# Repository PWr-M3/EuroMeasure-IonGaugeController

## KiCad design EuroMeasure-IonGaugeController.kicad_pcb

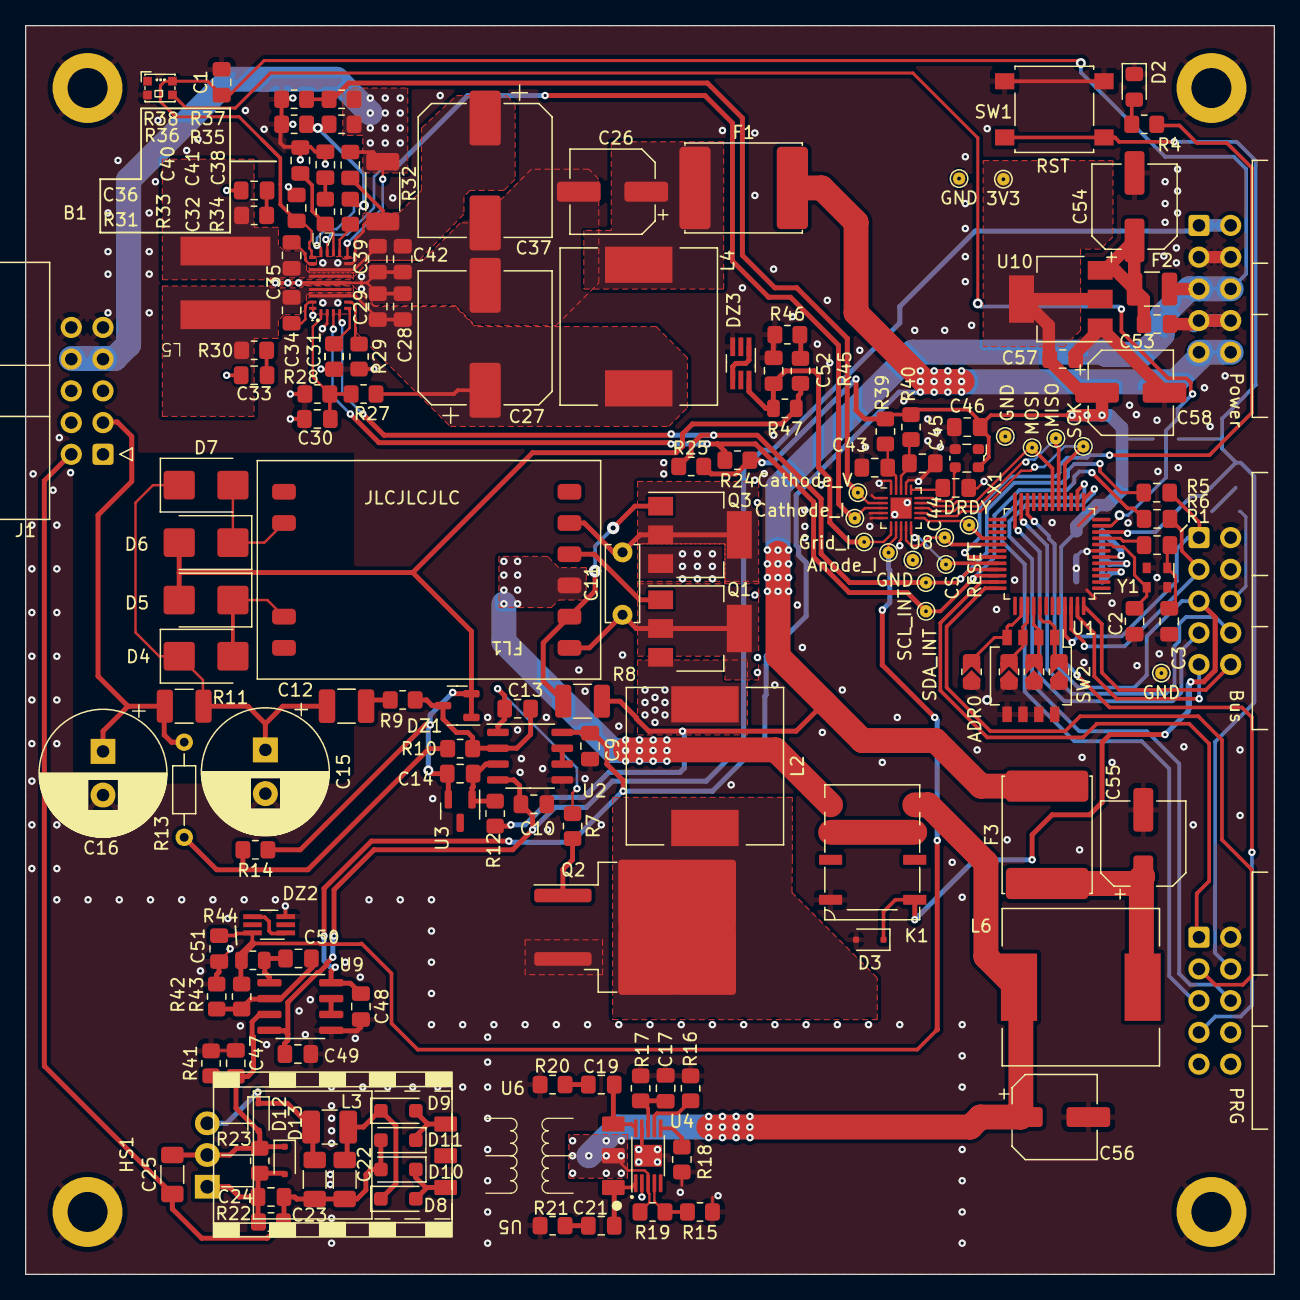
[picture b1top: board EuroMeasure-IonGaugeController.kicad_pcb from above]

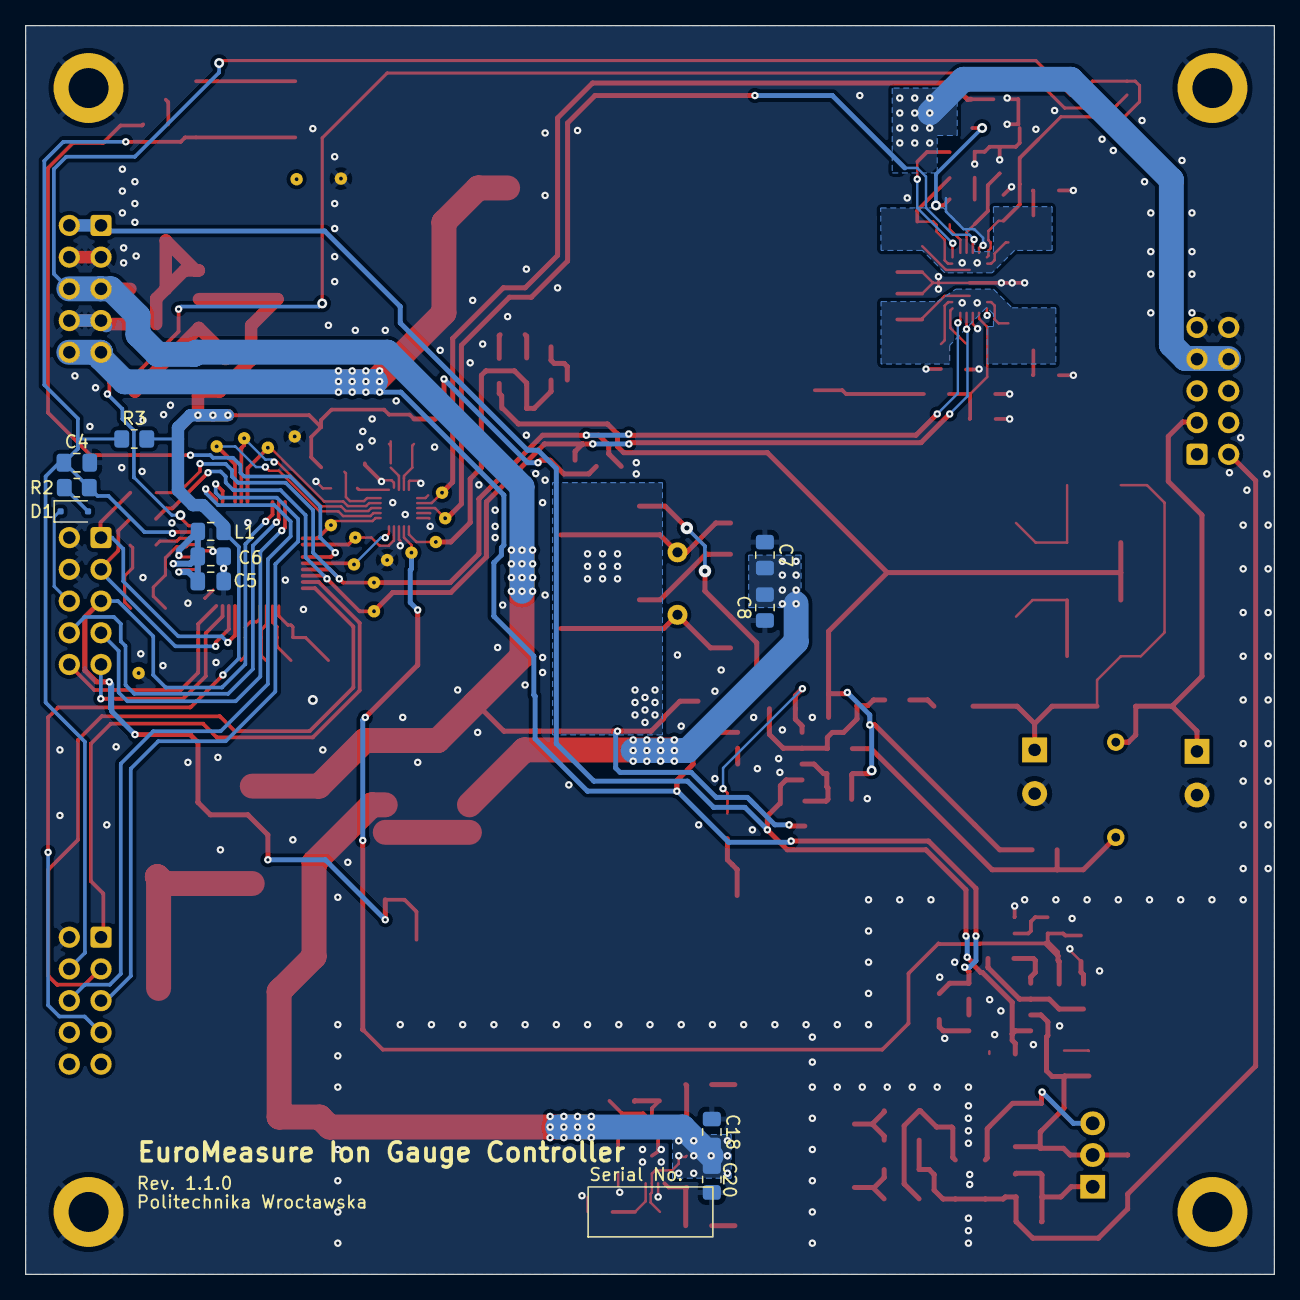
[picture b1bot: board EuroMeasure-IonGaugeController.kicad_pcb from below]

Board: 2 copper layers, 100.0 x 100.0 mm, 173 parts (11 on the bottom side), 107 nets.

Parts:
B1: EuroBoard; EuroMeasureLED
C1, C6, C7, C8, C18, C20, C24, C28, C29, C32, C39, C42, C43, C44, C45, C53, C57: 10u; C_0805_2012Metric_Pad1.18x1.45mm_HandSolder
C2, C3: 8p; C_0805_2012Metric_Pad1.18x1.45mm_HandSolder
C4, C5, C9, C10, C13, C14, C30, C34, C35, C38, C41, C46, C47, C48, C49: 100n; C_0805_2012Metric_Pad1.18x1.45mm_HandSolder
C11: 220n; C_Disc_D6.0mm_W2.5mm_P5.00mm
C12: 1n X7R; C_1210_3225Metric_Pad1.33x2.70mm_HandSolder
C15, C16: 3.3u 400V; CP_Radial_D10.0mm_P3.50mm
C17: 1uF; C_0805_2012Metric_Pad1.18x1.45mm_HandSolder
C19, C21, C33, C36: C_0805_2012Metric_Pad1.18x1.45mm_HandSolder
C22, C23, C25: 10u; C_1206_3216Metric_Pad1.33x1.80mm_HandSolder
C26, C55, C56: 220uF 50V; CP_Elec_6.3x7.7
C27, C37: 330uF 25V; CP_Elec_10x12.5
C31, C51, C52: 10n; C_0805_2012Metric_Pad1.18x1.45mm_HandSolder
C40: 100p; C_0805_2012Metric_Pad1.18x1.45mm_HandSolder
C50: 200p C0G; C_0805_2012Metric_Pad1.18x1.45mm_HandSolder
C54, C58: 220u; CP_Elec_6.3x7.7
D1, D3, D12, D13: 1N4148; D_SOD-323F
D2: RED; LED_0805_2012Metric_Pad1.15x1.40mm_HandSolder
D4, D5, D6, D7: MURS160BJ; D_SMB
D8: D_PMEG200G20ELRX; D_SOD-123F
D9, D10, D11: MURS160BJ; D_SOD-123F
DZ1: 14V; SOT-23-3
DZ2, DZ3: 2V4; SOT-363_SC-70-6_Handsoldering
F1, F3: Polyfuse 2A; Fuse_Littlefuse_3425L
F2: Polyfuse 0.5A; Fuse_1210_3225Metric
FL1: FL2015-4L; T_FL2015
HS1: Heatsink 274-3AB; 274-3AB
J1: Gauge Connector; IDC-Header_2x05_P2.54mm_Horizontal
JP1: ADR0; R_0805_2012Metric_Jumper
JP2: ADR1; R_0805_2012Metric_Jumper
JP3: ADR2; R_0805_2012Metric_Jumper
JP4: ADR3; R_0805_2012Metric_Jumper
K1: UD2-5NU; Relay_DPDT_Kemet_UC2_NU
L1: Ferrite; L_0805_2012Metric_Pad1.15x1.40mm_HandSolder
L2, L4, L6: 220u; L_12x12mm_H8mm
L3: 220u; L_1210_3225Metric_Pad1.42x2.65mm_HandSolder
L5: 8.2u; L_Bourns_SRP7030
Q1, Q3: FZT1053A; SOT-223-3_TabPin2
Q2: IRF540SPBF; TO-263-2
R1, R5, R6: 0R; C_0805_2012Metric_Pad1.18x1.45mm_HandSolder
R2, R3, R4, R9, R24, R25, R28, R38: 1k; R_0805_2012Metric_Pad1.20x1.40mm_HandSolder
R7, R12, R27, R37: 10k; R_0805_2012Metric_Pad1.20x1.40mm_HandSolder
R8: R_1210_820Ohm; R_1210_3225Metric_Pad1.30x2.65mm_HandSolder
R10: 470k; R_0805_2012Metric_Pad1.20x1.40mm_HandSolder
R11: 1k 0.5W; R_1210_3225Metric_Pad1.30x2.65mm_HandSolder
R13: 2M; R_Axial_DIN0204_L3.6mm_D1.6mm_P7.62mm_Horizontal
R14: 30k; R_0805_2012Metric_Pad1.20x1.40mm_HandSolder
R15: 1.5k; R_0805_2012Metric_Pad1.20x1.40mm_HandSolder
R16: 22k; R_0805_2012Metric_Pad1.20x1.40mm_HandSolder
R17: 50k; R_0805_2012Metric_Pad1.20x1.40mm_HandSolder
R18: 21k; R_0805_2012Metric_Pad1.20x1.40mm_HandSolder
R19: 2.2k; R_0805_2012Metric_Pad1.20x1.40mm_HandSolder
R20, R21, R30, R31: R_0805_2012Metric_Pad1.20x1.40mm_HandSolder
R22: 4.7k; R_0805_2012Metric_Pad1.20x1.40mm_HandSolder
R23: 240R; R_0805_2012Metric_Pad1.20x1.40mm_HandSolder
R26, R34: 0R; R_0805_2012Metric_Pad1.20x1.40mm_HandSolder
R29: 47k; R_0805_2012Metric_Pad1.20x1.40mm_HandSolder
R32: 20m 1%; R_2010_5025Metric_Pad1.40x2.65mm_HandSolder
R33, R36: 8.2k; R_0805_2012Metric_Pad1.20x1.40mm_HandSolder
R35: 100k; R_0805_2012Metric_Pad1.20x1.40mm_HandSolder
R39: 1; R_0805_2012Metric_Pad1.20x1.40mm_HandSolder
R40: 10; R_0805_2012Metric_Pad1.20x1.40mm_HandSolder
R41, R42: 1k 0.1% 5PPM; R_0805_2012Metric_Pad1.20x1.40mm_HandSolder
R43: 10k 0.1% 5PPM; R_0805_2012Metric_Pad1.20x1.40mm_HandSolder
R44, R47: 1k; R_0805_2012Metric
R45, R46: 100R 0.1% 5PPM; R_0805_2012Metric_Pad1.20x1.40mm_HandSolder
SW1: RST; SW_SPST_B3S-1000
SW2: SW_DIP_x04; SW_DIP_SPSTx04_Slide_Omron_A6H-4101_W6.15mm_P1.27mm
TP1: Cathode_V; TestPoint_Pad_D1.0mm
TP2: Cathode_I; TestPoint_Pad_D1.0mm
TP3: Anode_I; TestPoint_Pad_D1.0mm
TP4: Grid_I; TestPoint_Pad_D1.0mm
TP5, TP6, TP7, TP8: GND; TestPoint_Pad_D1.0mm
TP9: SCK; TestPoint_Pad_D1.0mm
TP10: MISO; TestPoint_Pad_D1.0mm
TP11: MOSI; TestPoint_Pad_D1.0mm
TP12: DRDY; TestPoint_Pad_D1.0mm
TP13: RESET; TestPoint_Pad_D1.0mm
TP14: CS; TestPoint_Pad_D1.0mm
TP15: SCL_INT; TestPoint_Pad_D1.0mm
TP16: SDA_INT; TestPoint_Pad_D1.0mm
TP17: 3V3; TestPoint_Pad_D1.0mm
U1: STM32G030CxT; LQFP-48_7x7mm_P0.5mm
U2: TL072; SO-8_3.9x4.9mm_P1.27mm
U3: 3.0V; SOT-23
U4: SN6507
U5: T_750316856; 750316856
U6: LM317HVT_TO-220-3; TO-220-3_Horizontal_TabUp
U7: TPS55289
U8: ADS131M04-WQFN; WQFN-20-1EP_3x3mm_P0.4mm_EP1.7x1.7mm
U9: OPA2187; SOIC-8_3.9x4.9mm_P1.27mm
U10: AZ1117-3V3; SOT-223-3_TabPin2
X1: 8.192MHz; Oscillator_SMD_ECS_2520MV-xxx-xx-4Pin_2.5x2.0mm
Y1: 16MHz; Oscillator_SMD_Abracon_ASDMB-4Pin_2.5x2.0mm

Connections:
+3.3V: B1.27 (3.3V), C46.2, C57.1, C58.1, L1.1, R3.2, R24.1, R25.1, R39.2, R40.2, TP17.1, U10.2 (VO), X1.4 (VDD)
+5V: B1.5 (5V), B1.6 (5V), B1.D4 (VCC), C1.1, C32.2, F2.1, F3.2, R8.2, R12.1, U7.18 (VCC)
+15V: B1.9 (15V), B1.10 (15V), C9.2, C48.1, F1.2, U2.8 (V+), U9.8 (V+)
-15V: B1.1 (-15V), B1.2 (-15V), C10.1, C49.2, U2.4 (V-), U9.4 (V-)
/ADC/1: R37.2, R38.1, TP1.1, U8.2 (AIN0N)
/ADC/2: TP2.1, U7.16 (CDC), U8.3 (AIN1N)
/ADC/3: C52.1, DZ3.6 (K), R47.2, TP4.1, U8.6 (AIN2N)
/ADC/4: C51.1, DZ2.6 (K), R43.2, R44.2, TP3.1, U8.7 (AIN3N)
/ADC/CLK: U8.15 (CLKIN), X1.3 (OUT)
/ADC/CS: TP14.1, U1.32 (PA10), U8.10 (~CS)
/ADC/DIN: TP11.1, U1.18 (PA7), U8.14 (DIN)
/ADC/DOUT: TP10.1, U1.17 (PA6), U8.13 (DOUT)
/ADC/DRDY: TP12.1, U1.28 (PA8), U8.11 (~DRDY)
/ADC/RESET: TP13.1, U1.29 (PA9), U8.9 (~SYNC/~RESET)
/ADC/SCLK: TP9.1, U1.16 (PA5), U8.12 (SCLK)
/ANODE: C22.1, C23.1, C24.1, C25.1, D10.2 (A), D11.2 (A), J1.2, R22.2
/Anode Current Measurement/IN: C25.2, C47.1, D12.2 (A), D13.1 (K), R23.1, R41.1, U6.2 (VO), U9.3 (+)
/Anode Supply/5V_IN: C18.2, C20.2, C56.1, K1.4, L6.2, R19.2, U4.3 (VCC), U5.2
/Anode Supply/SW1: C21.1, U4.1 (SW1), U5.1
/Anode Supply/SW2: C19.1, U4.10 (SW2), U5.3
/Backplane connector/GP0: B1.17 (GP0), U1.24 (PB12)
/Backplane connector/GP1: B1.18 (GP1), U1.23 (PB11)
/Backplane connector/RDY: B1.20 (RDY), U1.48 (PB9)
/Backplane connector/RST: B1.16 (RST), D1.1 (K)
/Backplane connector/RST_LOCAL: B1.24 (RST), C4.1, R2.1, R3.1, SW1.2, U1.10 (NRST)
/Backplane connector/RX: B1.25 (RX), U1.14 (PA3)
/Backplane connector/SCL: B1.11 (SCL), R5.1, U1.45 (PB6)
/Backplane connector/SDA: B1.13 (SDA), R6.2, U1.46 (PB7)
/Backplane connector/SWCLK: B1.23 (SWCLK), U1.36 (PA14)
/Backplane connector/SWDIO: B1.21 (SWDIO), U1.35 (PA13)
/Backplane connector/TRG: B1.19 (TRG), U1.47 (PB8)
/Backplane connector/TX: B1.26 (TX), U1.13 (PA2)
/Backplane connector/~LOCKOUT: B1.15 (~LOCKOUT), D3.1 (K), K1.1, U1.22 (PB10)
/CATHODE: C38.2, J1.7, J1.8, R32.2, R35.1, R37.1, U7.13 (ISN)
/Cathode Supply/15V_FILTERED: C27.1, C28.2, C29.2, L4.2, R27.1, U7.7 (VIN)
/Cathode Supply/SCL: R5.2, R25.2, TP15.1, U1.33 (PA11), U7.4 (SDA)
/Cathode Supply/SDA: R6.1, R24.2, TP16.1, U1.34 (PA12), U7.3 (SCL)
/Cathode Supply/SW1: C34.1, L5.1, R30.2, U7.8 (SW1)
/GRID: C16.1, J1.3, R11.2, R13.2
/Grid Supply/5V_Lockouted: C7.2, C8.2, FL1.3, K1.5
/Grid Supply/GRID_AC0: D4.2 (A), D5.1 (K), FL1.9
/Grid Supply/GRID_AC1: D6.1 (K), D7.2 (A), FL1.8
/Grid Supply/GRID_Unfiltered: C12.1, C15.1, D4.1 (K), D7.1 (K), R11.1
/Grid Supply/heatsink_1: C11.1, FL1.1, Q1.2 (C)
/Grid Supply/heatsink_2: C11.2, FL1.5, Q3.2 (C)
/Grid Supply/heatsink_3: L2.1, Q1.3 (E), Q3.3 (E)
/Grid Supply/heatsink_4: L2.2, Q2.2 (D)
/MCU/3V3_MCU: C5.1, C6.1, L1.2, U1.4 (VBAT), U1.5 (VREF+), U1.6 (VDD/VDDA)
/MCU/ADR0: JP1.1, SW2.4, U1.38 (PD0)
/MCU/ADR1: JP2.1, SW2.3, U1.39 (PD1)
/MCU/ADR2: JP3.1, SW2.2, U1.40 (PD2)
/MCU/ADR3: JP4.1, SW2.1, U1.41 (PD3)
/MCU/LED: R4.2, U1.31 (PC7)
/MCU/OSC_IN: R1.2, U1.9 (PF1-OSC_OUT)
/MCU/OSC_OUT: C2.1, U1.8 (PF0-OSC_IN), Y1.3
/MCU/RGB_LED: B1.D3 (DI), U1.11 (PA0)
/PSU/5V_FUSED: C53.1, C54.1, F2.2, U10.3 (VI)
GND: B1.3 (GND), B1.4 (GND), B1.7 (GND), B1.8 (GND), B1.12 (GND), B1.14 (GND), B1.22 (GND), B1.D2 (GND), C1.2, C2.2, C3.2, C4.2, C5.2, C6.2, C7.1, C8.1, C9.1, C10.2, C15.2, C16.2, C17.1, C18.1, C20.1, C26.2, C27.2, C28.1, C29.1, C30.1, C31.2, C32.1, C33.2, C36.2, C37.2, C39.1, C40.1, C41.1, C42.1, C43.1, C44.2, C45.2, C46.1, C47.2, C48.2, C49.1, C51.2, C52.2, C53.2, C54.2, C55.2, C56.2, C57.2, C58.2, D2.1 (K), D3.2 (A), DZ2.3 (K), DZ3.3 (K), J1.9, J1.10, JP1.2, JP2.2, JP3.2, JP4.2, K1.8, Q2.3 (S), R15.1, R16.1, R17.1, R18.1, R20.2, R21.2, R26.2, R28.2, R29.2, R36.2, R38.2, R41.2, R42.2, R46.2, SW1.1, SW2.5, SW2.6, SW2.7, SW2.8, TP5.1, TP6.1, TP7.1, TP8.1, U1.7 (VSS/VSSA), U2.5 (+), U4.2 (GND), U4.9 (GND), U4.11 (GND), U7.2 (MODE), U7.9 (PGND), U7.17 (AGND), U7.21 (EXTVCC), U8.1 (AIN0P), U8.4 (AIN1P), U8.5 (AIN2P), U8.8 (AIN3P), U8.17 (DGND), U8.20 (AGND), U8.21 (THERMAL(AGND)), U9.5 (+), U10.1 (GND), X1.2 (GND), Y1.2, Y1.4
GNDD: C14.1, D5.2 (A), D6.2 (A), DZ1.1 (A), DZ1.2 (A), R14.1, R45.1, R47.1, U3.2 (A)
unnamed: C3.1, R1.1, Y1.1
unnamed: C12.2, R9.1
unnamed: C13.1, R7.1, U2.1
unnamed: C19.2, R20.1
unnamed: C21.2, R21.1
unnamed: C26.1, F1.1, L4.1
unnamed: C33.1, R30.1
unnamed: C36.1, R31.1
unnamed: C41.2, R33.2
unnamed: C50.2, R44.1, U9.1
unnamed: C55.1, F3.1, L6.1
unnamed: D1.2 (A), R2.2
unnamed: D2.2 (A), R4.1
unnamed: C22.2, D8.1 (K), D9.1 (K), L3.1
unnamed: D8.2 (A), D10.1 (K), U5.6
unnamed: D9.2 (A), D11.1 (K), U5.4
unnamed: C23.2, D12.1 (K), L3.2, U6.3 (VI)
unnamed: C24.2, D13.2 (A), R22.1, R23.2, U6.1 (ADJ)
unnamed: C13.2, DZ1.3 (K), R9.2, R10.2, U2.2 (-)
unnamed: DZ2.1 (A), DZ2.4 (A)
unnamed: DZ3.1 (A), DZ3.4 (A)
unnamed: K1.3, K1.6
unnamed: FL1.4, Q1.1 (B)
unnamed: Q2.1 (G), R7.2
unnamed: FL1.2, Q3.1 (B), R8.1
unnamed: R10.1, R13.1, R14.2
unnamed: R34.2, R35.2, R36.1
unnamed: R45.2, R46.1
unnamed: C14.2, R12.2, U2.3 (+), U3.1 (K)
unnamed: U2.6 (-), U2.7
unnamed: R16.2, U4.7 (CLK)
unnamed: R15.2, R19.1, U4.4 (EN/UVLO)
unnamed: R18.2, U4.6 (SR)
unnamed: C17.2, R17.2, U4.8 (SS/ILIM)
unnamed: C34.2, U7.20 (BOOT1)
unnamed: C35.2, U7.19 (BOOT2)
unnamed: C40.2, R33.1, U7.15 (COMP)
unnamed: C31.1, R26.1, U7.5 (DITH/SYNC)
unnamed: C30.2, R27.2, R28.1, U7.1 (EN/UVLO)
unnamed: R34.1, U7.14 (FB/~INT)
unnamed: R29.1, U7.6 (FSW)
unnamed: C37.1, C38.1, C39.2, C42.2, R32.1, U7.11 (VOUT), U7.12 (ISP)
unnamed: C35.1, L5.2, R31.2, U7.10 (SW2)
unnamed: C43.2, R39.1, U8.19 (AVDD)
unnamed: C44.1, U8.16 (CAP)
unnamed: C45.1, R40.1, U8.18 (DVDD)
unnamed: C50.1, R42.1, R43.1, U9.2 (-)
unnamed: U9.6 (-), U9.7

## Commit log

2023-10-17 Rename to Ion Gauge Controller
2023-10-17 First schematic draft
2023-11-04 A lot of work
2023-11-11 Copper layout done
2023-11-11 Clean DRC
2023-12-09 Final 1.0.0 version
2023-12-09 Generated BOM and found replacements
2023-12-09 Generated gerbers
2024-01-20 Revision 1.1.0. DRC clean
2024-01-28 Everything clear. Gerbers generated
2024-01-28 Exported auxiliary files
